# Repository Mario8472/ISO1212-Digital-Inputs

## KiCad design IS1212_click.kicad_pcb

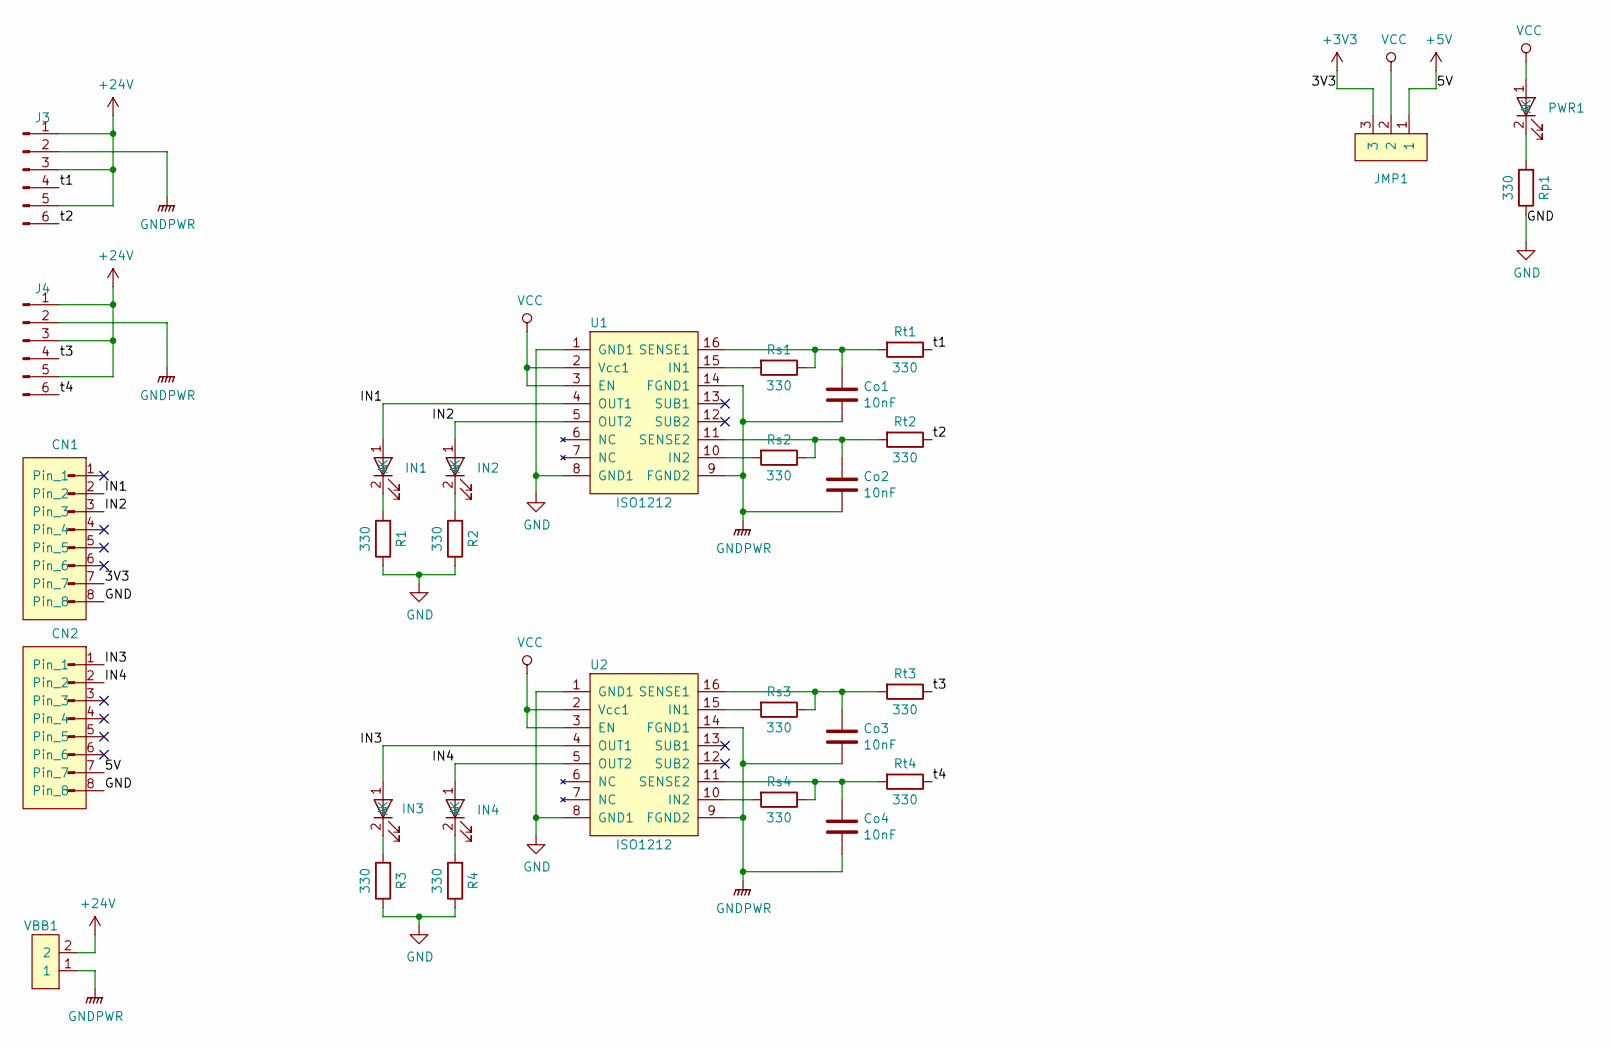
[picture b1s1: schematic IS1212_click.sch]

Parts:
CN1, CN2: HeaderPin_1x8_2.54mm; PinHeader_1x08_P2.54mm_Vertical
Co1, Co2, Co3, Co4: 10nF; C_0805_2012Metric
IN1, IN2, IN3, IN4: LED0805
J3, J4: Conn_01x06_Male; PinHeader_1x06_P2.54mm_Vertical
JMP1: JUMPER_0805; Jumper_0805
PWR1: LED0805
R1, R2, R3, R4: 330; R_0805_2012Metric
Rp1: 330; R_0805_2012Metric
Rs1, Rs2, Rs3, Rs4: 330; R_1206_3216Metric
Rt1, Rt2, Rt3, Rt4: 330; R_1206_3216Metric
U1, U2: ISO1212
VBB1: PCB_Terminal_2.54mm_2way

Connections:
+3V3: CN1.7, JMP1.3
+5V: CN2.7, JMP1.1
+24V: J3.1, J3.3, J3.5, J4.1, J4.3, J4.5, VBB1.2
/IN1: CN1.2, IN1.1 (A), U1.4 (OUT1)
/IN2: CN1.3, IN2.1 (A), U1.5 (OUT2)
/IN3: CN2.1, IN3.1 (A), U2.4 (OUT1)
/IN4: CN2.2, IN4.1 (A), U2.5 (OUT2)
/t1: J3.4, Rt1.1
/t2: J3.6, Rt2.1
/t3: J4.4, Rt3.1
/t4: J4.6, Rt4.1
GND: CN1.8, CN2.8, R1.1, R2.1, R3.1, R4.1, Rp1.1, U1.1 (GND1), U1.8 (GND1), U2.1 (GND1), U2.8 (GND1)
GNDPWR: Co1.2, Co2.2, Co3.2, Co4.2, J3.2, J4.2, U1.9 (FGND2), U1.14 (FGND1), U2.9 (FGND2), U2.14 (FGND1), VBB1.1
unnamed: Co1.1, Rs1.1, Rt1.2, U1.16 (SENSE1)
unnamed: Co2.1, Rs2.1, Rt2.2, U1.11 (SENSE2)
unnamed: Co3.1, Rs3.1, Rt3.2, U2.16 (SENSE1)
unnamed: Co4.1, Rs4.1, Rt4.2, U2.11 (SENSE2)
unnamed: IN1.2 (K), R1.2
unnamed: IN2.2 (K), R2.2
unnamed: IN3.2 (K), R3.2
unnamed: IN4.2 (K), R4.2
unnamed: PWR1.2 (K), Rp1.2
unnamed: Rs1.2, U1.15 (IN1)
unnamed: Rs2.2, U1.10 (IN2)
unnamed: Rs3.2, U2.15 (IN1)
unnamed: Rs4.2, U2.10 (IN2)
VCC: JMP1.2, PWR1.1 (A), U1.2 (Vcc1), U1.3 (EN), U2.2 (Vcc1), U2.3 (EN)

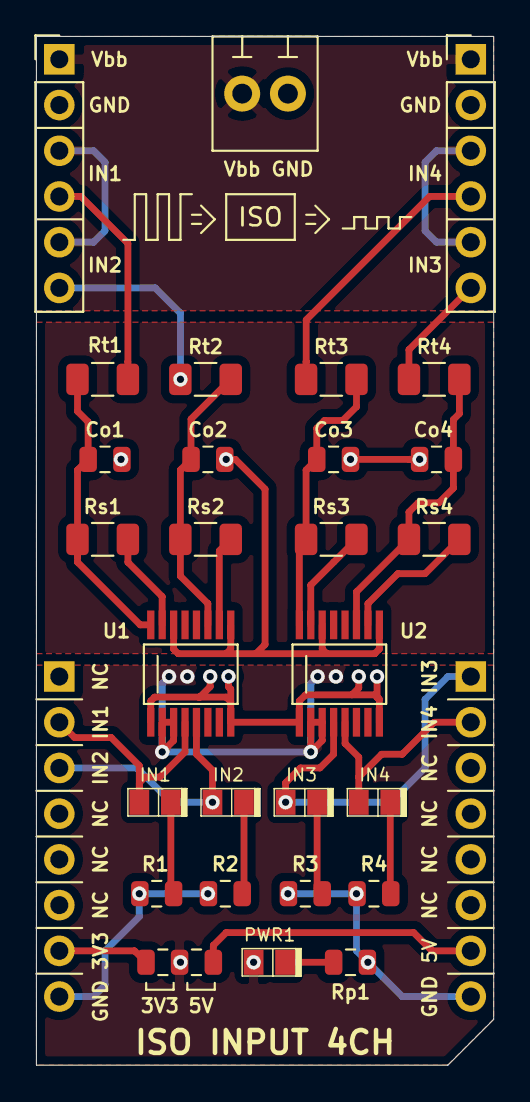
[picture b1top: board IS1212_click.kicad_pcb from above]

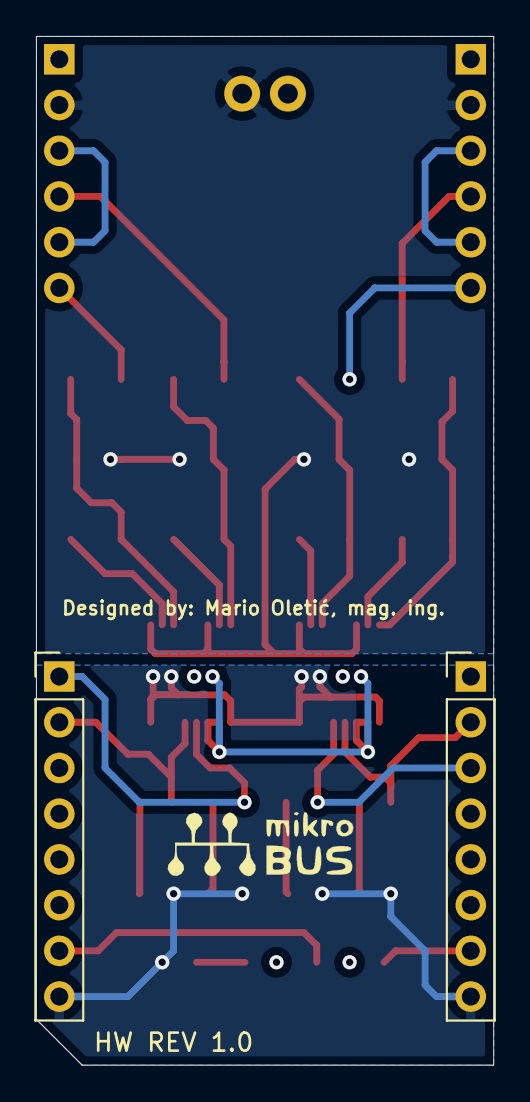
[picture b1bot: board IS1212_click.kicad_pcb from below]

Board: 2 copper layers, 25.4 x 57.2 mm, 30 parts (2 on the bottom side), 27 nets.
